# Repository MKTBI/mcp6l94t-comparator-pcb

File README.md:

# 🔌 MCP6L94T Analog Comparator Board — BSc PCB Design

> A 4-channel voltage threshold detector built around the MCP6L94T quad op-amp,
> fully designed in KiCad from schematic to 3D render.

📄 BSc Mechatronics Engineering · 2020

---

## 📌 Project Overview

This was my first complete PCB design. The goal was to design a functional analog comparator circuit using the MCP6L94T op-amp, route it on a real PCB, and produce a manufacturable board file , handling the full workflow from schematic capture to Gerber export and 3D verification.

The circuit uses four comparator channels to drive individual LEDs, powered by a 9V battery with a push-to-test function for manual verification.

---

## ⚙️ Circuit Overview

| Property | Value |
|---|---|
| Core IC | MCP6L94T-E/SL — Quad Op-Amp (SOP-14) |
| Supply | 9V DC battery (BT1) |
| Voltage ladder | R2 (3.3kΩ) + R3–R6 (4× 10kΩ) — sets four inverting thresholds |
| Input reference | D5 (6V Zener) + R1 (10kΩ) + R11 (1MΩ) — stable ~6V on VIN+ |
| Input clamping | D3 (6V Zener) + R2 (3.3kΩ) |
| Outputs | 4× LED indicators with 3.3kΩ current limiters (R7–R10) |
| Bypass capacitor | 0.1µF (C1) on VDD |
| Reverse polarity | D2 diode protection |
| Test function | Push-to-test button — forces all LEDs ON simultaneously |
| EDA Tool | KiCad 5.1.5 |

---

## 💡 How It Works

The circuit is a **4-channel voltage threshold detector** built around the MCP6L94T quad op-amp in open-loop comparator configuration.

**Resistor ladder (VIN− inputs):**
- R2–R6 form a voltage divider from 9V to GND
- Each ladder tap connects to one VIN− (inverting input):
  - Pin 2 VINA− → tap between R2 and R3
  - Pin 6 VINB− → tap between R3 and R4
  - Pin 9 VINC− → tap between R4 and R5
  - Pin 13 VIND− → tap between R5 and R6
- This creates four decreasing reference thresholds on the inverting inputs

**Reference signal (VIN+ inputs):**
- D5 (6V Zener) + R1 (10kΩ) + R11 (1MΩ) set a stable ~6V signal
- This fixed voltage feeds the non-inverting VIN+ inputs of the comparators

**Comparator logic:**
- Each channel compares the fixed ~6V input against its ladder threshold
- If VIN+ > VIN− → output HIGH → LED lights up
- If VIN+ < VIN− → output LOW → LED stays off
- LEDs activate based on which thresholds the input voltage crosses

**Push-to-test:**
- Connects 9V directly to all outputs simultaneously
- All 4 LEDs light up — confirms all LEDs and output paths are functional

---

## 🖼 Board Preview

### Front Side (F.Cu)

### Back Side (B.Cu)

### 3D Render — Front

### 3D Render — Back

---

## 🛠 Design Workflow

1. **Schematic capture** — all components placed and connected in KiCad Schematic Editor
2. **PCB layout** — manual trace routing, component placement optimized for signal flow
3. **Gerber export** — full layer set exported for fabrication readiness
4. **Drill file export** — PTH and NPTH drill files generated
5. **3D render** — front and back verification before finalization
6. **Design review** — identified and corrected placement issues caught only in 3D view

---

## 📁 Repository Structure

```
mcp6l94t-comparator-pcb/
│
├── schematic/
│   ├── schematic.sch           
│   └── schematic.pdf      
│
├── pcb/
│   └── board.kicad_pcb
│
├── gerbers/
│   ├── F_Cu.gbr
│   ├── B_Cu.gbr
│   ├── F_Mask.gbr
│   ├── B_Mask.gbr
│   ├── F_Paste.gbr
│   ├── B_Paste.gbr
│   ├── F_SilkS.gbr
│   ├── B_SilkS.gbr
│   ├── Edge_Cuts.gbr
│   ├── PTH.drl
│   └── NPTH.drl
│
├── renders/
│   ├── pcb_front.png
│   ├── pcb_back.png
│   ├── 3d_front.png
│   └── 3d_back.png
│
├── mcp6l94t-comparator-pcb.pro
└── README.md
```

---

## 🔑 Key Learnings

- **3D rendering is not optional** — caught placement conflicts completely invisible in 2D layout
- **Ground planes matter** — routing without a solid copper fill creates unnecessary noise risk; first thing I'd fix in a redesign
- **SMD footprint sizing** — learned to balance component size against manual solderability

---

## 🔮 What I'd Do Differently Today

- Add a copper fill ground plane on both layers
- Tighten trace routing around the IC — reduce stub lengths
- Add test points on each comparator output for easier probing
- Use a regulated 5V supply instead of raw 9V battery

---

## 👤 Author

**Seyed Danial Maktabi**
BSc Mechatronics Engineering | MSc Data Analytics

---

## 📄 License

Open hardware — feel free to reference or adapt with attribution.

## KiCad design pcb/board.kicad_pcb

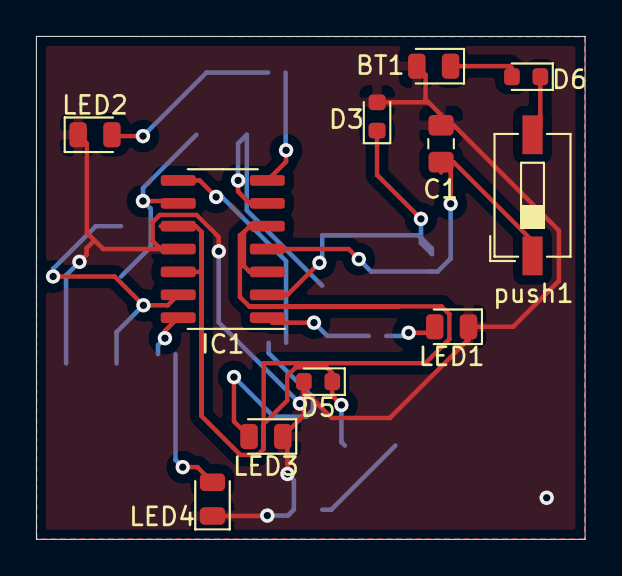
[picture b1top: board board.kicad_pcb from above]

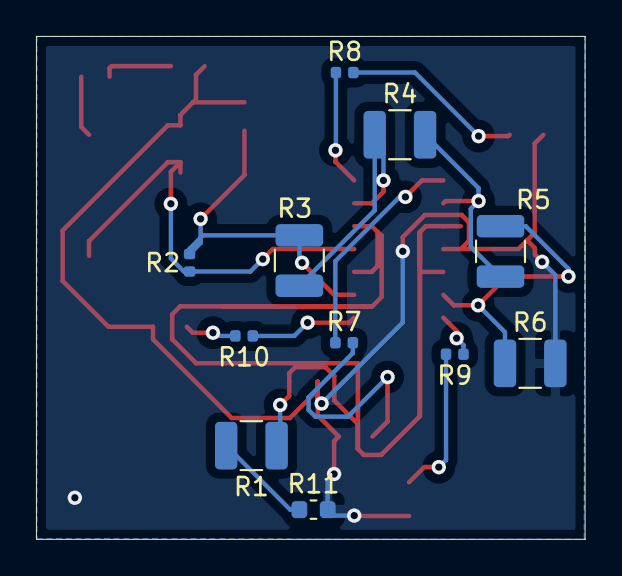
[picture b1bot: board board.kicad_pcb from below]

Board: 2 copper layers, 30.5 x 27.9 mm, 22 parts (11 on the bottom side), 18 nets.

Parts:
BT1: 9Vdc; LED_0805_2012Metric
C1: 0.1f; C_0805_2012Metric_Pad1.15x1.40mm_HandSolder
D3, D5: 6V; D_0603_1608Metric
D6: D2; D_0603_1608Metric
IC1: MCP6L94T-E_SL; SOIC-14_3.9x8.7mm_P1.27mm
LED1, LED2, LED3, LED4: LED; LED_0805_2012Metric
R1, R3, R4, R5, R6: 10K; R_1210_3225Metric
R2, R7, R8, R9, R10: 3.3K; R_0402_1005Metric
R11: 1M; R_0603_1608Metric
push1: push to test; SW_DIP_SPSTx01_Slide_6.7x4.1mm_W6.73mm_P2.54mm_LowProfile_J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

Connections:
GND: BT1.2, C1.2, D3.2, D5.2, IC1.11, LED1.1, LED2.1, LED3.1, LED4.1, R6.2, R11.2
unnamed: BT1.1, D6.2
unnamed: C1.1, IC1.4, R2.1, push1.1
unnamed: D3.1, IC1.2, R2.2, R3.1
unnamed: D5.1, IC1.3, IC1.5, IC1.10, IC1.12, R1.1
unnamed: D6.1, push1.2
unnamed: IC1.1, R10.1
unnamed: IC1.6, R3.2, R4.1
unnamed: IC1.7, R8.1
unnamed: IC1.8, R7.1
unnamed: IC1.9, R4.2, R5.1
unnamed: IC1.13, R5.2, R6.1
unnamed: IC1.14, R9.1
unnamed: LED1.2, R10.2
unnamed: LED2.2, R8.2
unnamed: LED3.2, R7.2
unnamed: LED4.2, R9.2
unnamed: R1.2, R11.1

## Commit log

2026-05-20 Update README
    Removed job title and location from author section.
2026-05-20 Updated README
    Updated educational background and EDA tool version in README.
2026-05-21 rm README.md
2026-05-21 README.md
